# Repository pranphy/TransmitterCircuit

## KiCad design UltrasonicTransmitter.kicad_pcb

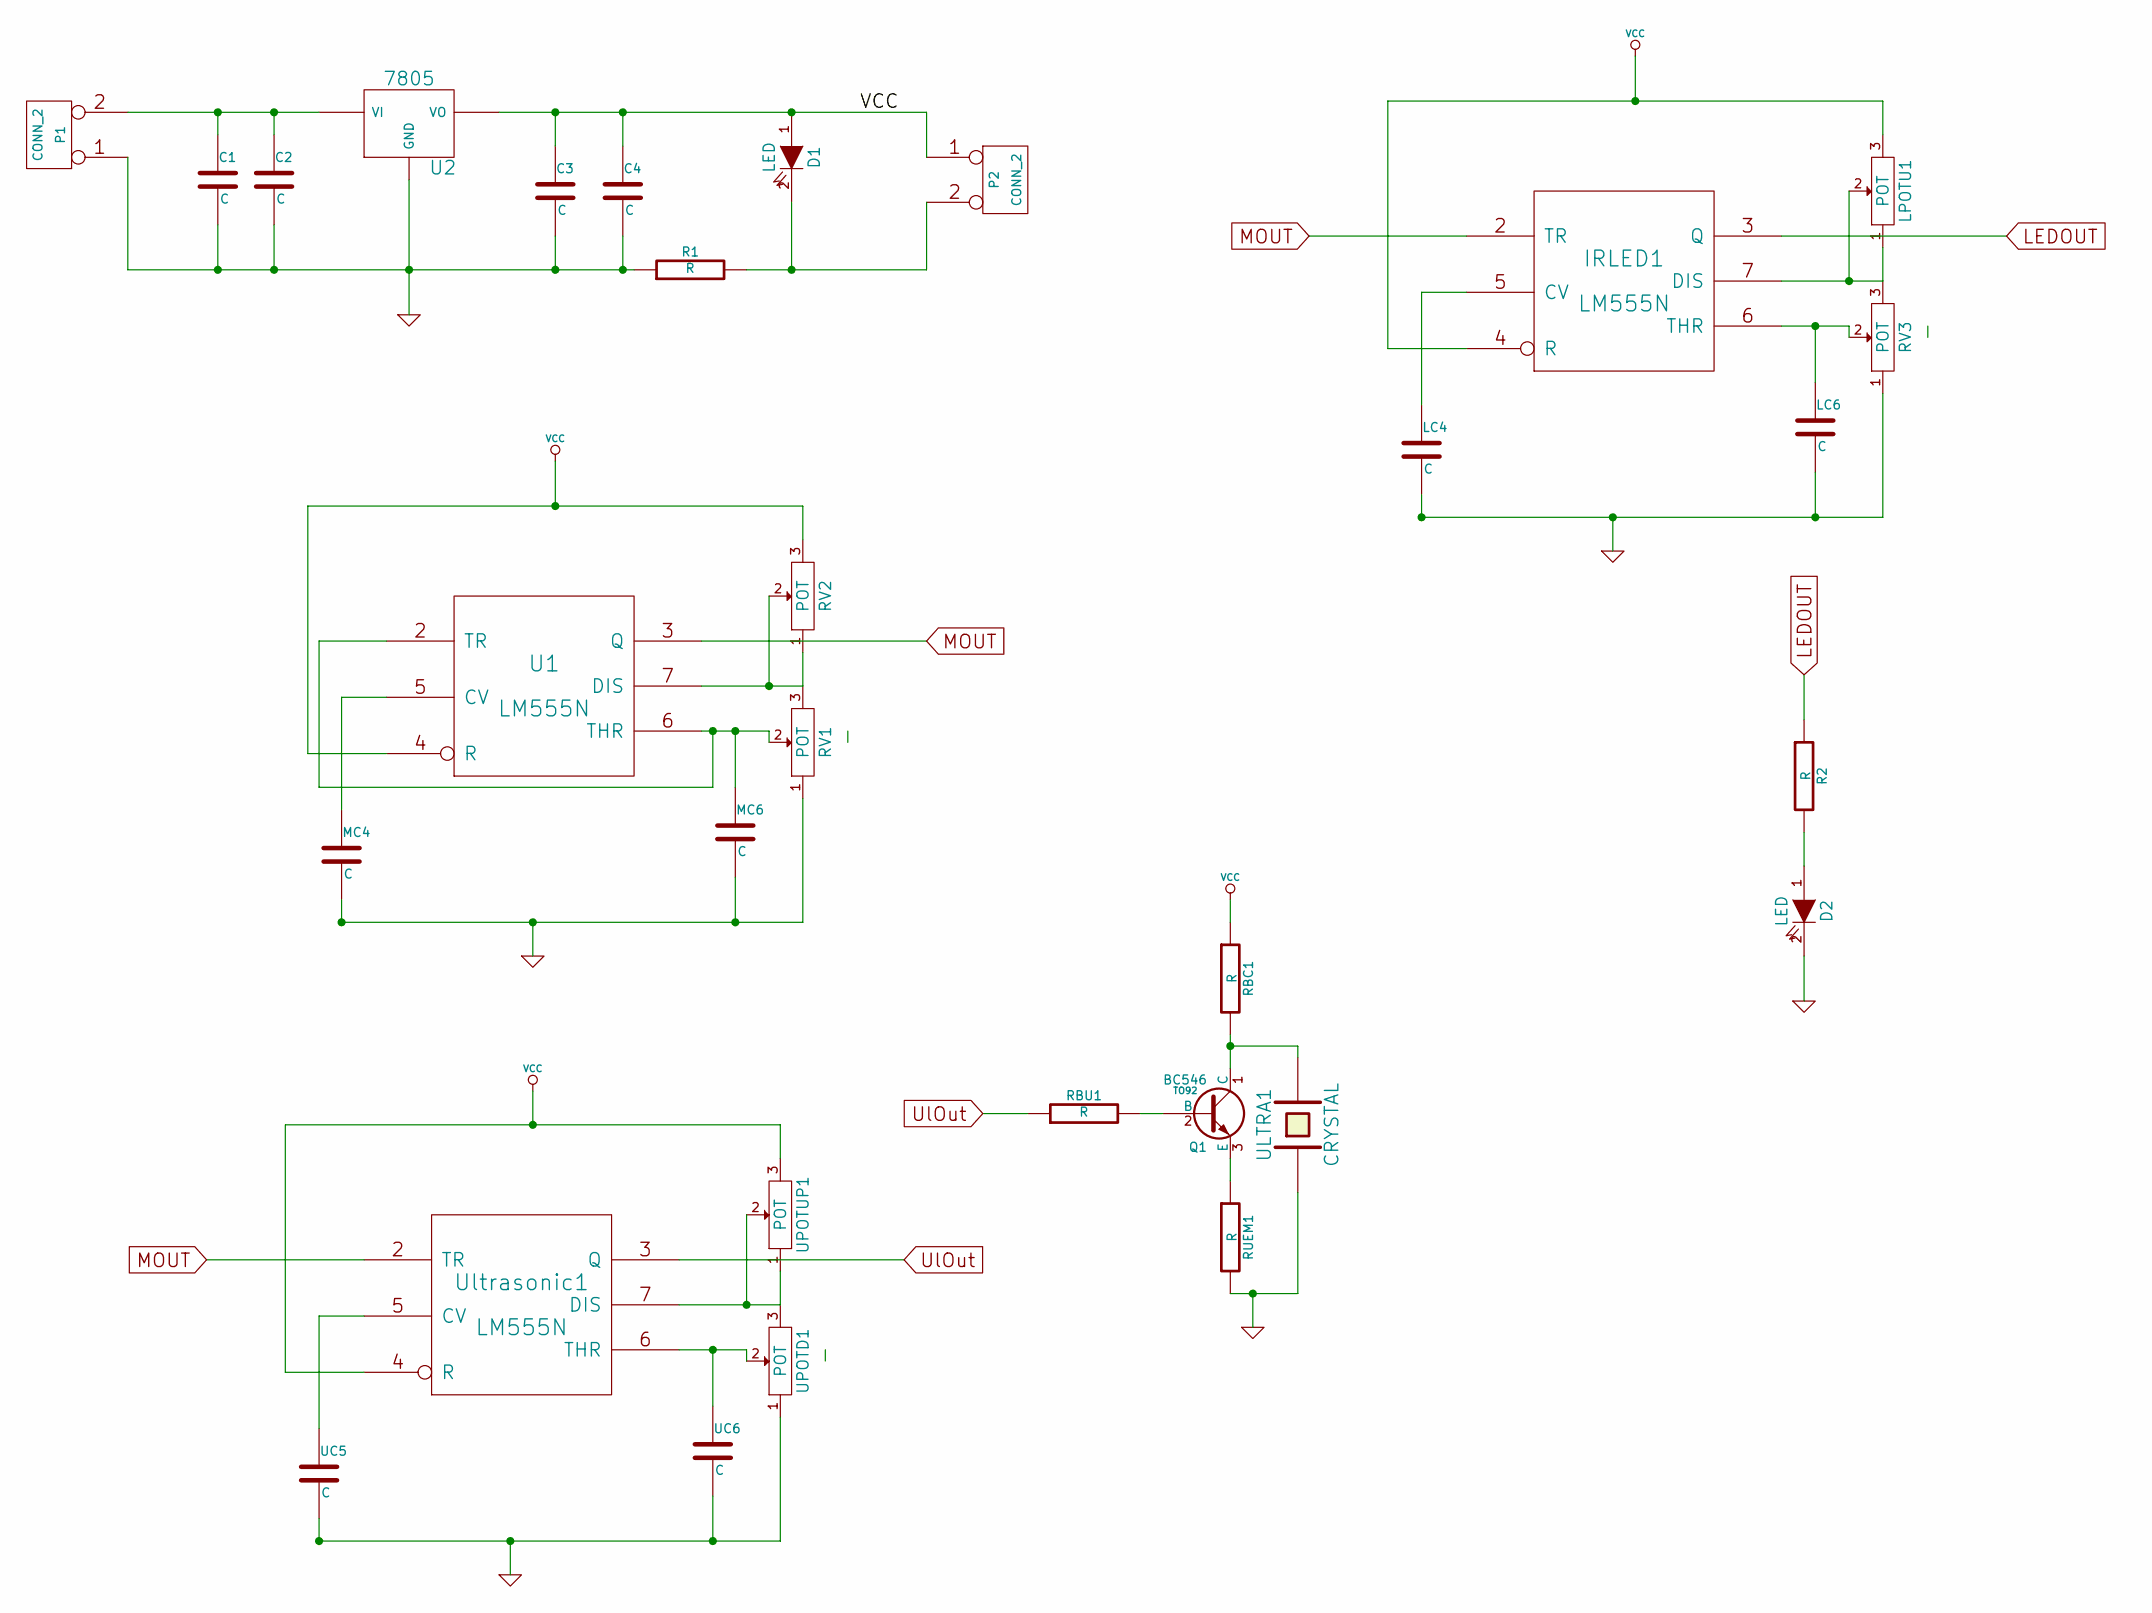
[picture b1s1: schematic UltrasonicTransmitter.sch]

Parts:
C1, C2, C3, C4: C
D1, D2: LED
IRLED1: LM555N
LC4, LC6: C
LPOTU1: POT
MC4, MC6: C
P1, P2: CONN_2
Q1: BC546; TO92
R1, R2: R
RBC1: R
RBU1: R
RUEM1: R
RV1, RV2, RV3: POT
U1: LM555N
U2: 7805
UC5, UC6: C
ULTRA1: CRYSTAL
UPOTD1: POT
UPOTUP1: POT
Ultrasonic1: LM555N

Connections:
GND: C1.2, C2.2, C3.2, C4.2, D2.2 (K), IRLED1.1 (GND), LC4.2, LC6.2, MC4.2, MC6.2, P1.1, R1.1, RUEM1.2, RV1.1, RV3.1, U1.1 (GND), U2.GND, UC5.2, UC6.2, ULTRA1.1, UPOTD1.1, Ultrasonic1.1 (GND)
LEDOUT: IRLED1.3 (Q), R2.1
MOUT: IRLED1.2 (TR), U1.3 (Q), Ultrasonic1.2 (TR)
unnamed: MC4.1, U1.5 (CV)
unnamed: RV1.3, RV2.1, RV2.2, U1.7 (DIS)
unnamed: IRLED1.6 (THR), LC6.1, RV3.2
unnamed: D1.2 (K), P2.2 (PM), R1.2
unnamed: IRLED1.5 (CV), LC4.1
unnamed: MC6.1, RV1.2, U1.2 (TR), U1.6 (THR)
unnamed: Q1.3 (E), RUEM1.1
unnamed: UPOTD1.3, UPOTUP1.1, UPOTUP1.2, Ultrasonic1.7 (DIS)
unnamed: D2.1 (A), R2.2
unnamed: Q1.2 (B), RBU1.2
unnamed: Q1.1 (C), RBC1.2, ULTRA1.2
unnamed: IRLED1.7 (DIS), LPOTU1.1, LPOTU1.2, RV3.3
unnamed: UC6.1, UPOTD1.2, Ultrasonic1.6 (THR)
unnamed: UC5.1, Ultrasonic1.5 (CV)
unnamed: C1.1, C2.1, P1.2 (PM), U2.VI
UlOut: RBU1.1, Ultrasonic1.3 (Q)
VCC: C3.1, C4.1, D1.1 (A), IRLED1.4 (R), IRLED1.8 (VCC), LPOTU1.3, P2.1, RBC1.1, RV2.3, U1.4 (R), U1.8 (VCC), U2.VO, UPOTUP1.3, Ultrasonic1.4 (R), Ultrasonic1.8 (VCC)

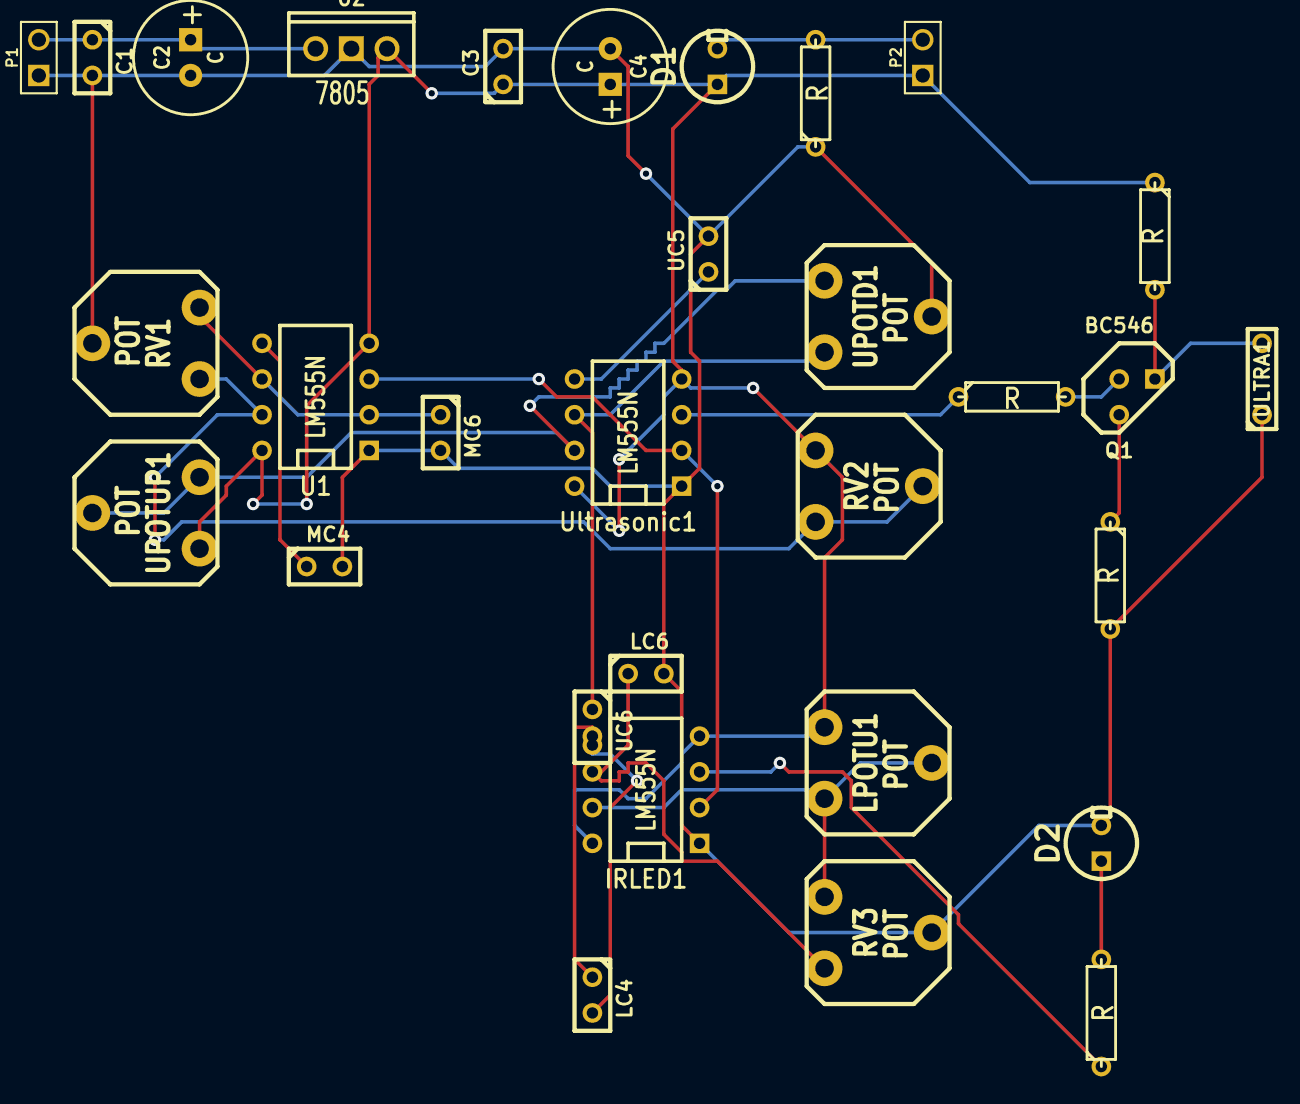
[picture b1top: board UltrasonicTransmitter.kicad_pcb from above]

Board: 2 copper layers, 31 parts (0 on the bottom side), 20 nets.

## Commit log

2015-08-10 First Commit of component placed
